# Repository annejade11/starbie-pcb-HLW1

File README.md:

# Cheesie PCB

In this project, I used the pre-existing Starbie tutorial repo by SharKingStudios to make my own "Cheesie" PCB build for week one of the Half Life challenge.

Before this project, I had never worked with PCBs or physical hardware before, but it's something I've been meaning to get into for a long time as I started coding a bit over a year ago. Ever since I started coding and 3D printing things on printers at my school, I just thought it would be so cool to be able to code my own product, then put it together in hardware and print a beautiful design for it. The concept of being my own little "factory" is so cool to me and this first week of Half Life has been the perfect opportunity for me to start learning something I just haven't made the time for before. 

So let's start with the basics.

What is Starbie?

Starbie is a small pcb with a 128x64 pixel OLED screen that displays a sprite of your choice. It has different activities, like napping or playing, and also has some mood bars for energy, joyfulness, and fullness. The tutorial repo describes it as a kind of "desktop tomadachi" and I honestly think that's a perfect description. It uses a DHT11 to detect temperature and humidity as well as an MPU6050 to detect movement, so it senses when you shake it and gives you a digital reaction. It's super cute and the tutorial makes it very beginner friendly.

My Process

Part 1: Hardware

The first part of building Starbie is designing it. I chose to use KiCad, as that's what's recommended by Half Life and also what the tutorial repo uses. I followed the instructions to design the schematic, which is basically all the components you're going to need labeled with what each output/input is recieving/sending.

Here's what mine looked like:

The next step in PCB design is routing, which means visually connecting everything so that you know where all the soldering and stuff is going to go. Because the lines can't cross over each other otherwise signals will mix, this step is super important because you're making sure everything can be connected. In my experience with Starbie, I actually had to change the order of ports (as well as the rotation and positioning of components) multiple times because I would end up in a situation where a connection couldn't get from A to B without crossing over a bunch of other connections. I also learned that the board has two sides, so some connections which just couldn't all fit on the front went on the back side of the PCB. I added some cute stickers to the PCB too (as well as some holes for mounting, but this is fully optional I just figured I might want to screw my PCB into a case). 

Here's the final result:

The red connections are the front, while that one thick blue line is what I have on the back of the PCB.

KiCad also has a really cool feature where you can see a 3D rendering of your PCB once you've routed it.

Seeing a (kind of) physical rendering of my work was super gratifying.

Part 2: Software

The next part of building Starbie was to do the code. The tutorial repo actually gives you a set of code already in case you don't know how, but I wanted to do some of it myself. Unfortunately, I didn't have the time to really dig into it as much as I might have liked, but I still wanted to customize it. (Note: I did have to edit the ports as I ended up moving them around in a different placement than the tutorial did, and anyone doing this should verify they have the same ports as what's in the code!)

The first thing I did was make my own sprite. I used a web-based sprite generator (not AI, just a platform that lets you draw pixelated sprites) called piskel. I made a fun little Peacock who remains unnamed, but I think she turned out very cute! For now I'll just go with Princess because the word "Peacock" contains the word "Pea" which reminds me of the Princess and the Pea, but I promise I'll choose something better later. 

Then, because you can't just drag and drop an image into code and say "draw this", I used a link from the tutorial to turn the photo into code. Here's what that looked like when it was done:

While I can't say I understand how every number works, my impression is that it's instructions that tell the code if each pixel on a 32 x 32 pixel grid is black or white. The screen I'm using can only display one color, which is white, (plus black when it's off), so the code shouldn't need to specify the exact shade of blue or gray for each pixel.

Note: Much of the following section is explaining functions and if statements for non-coders. If you already know this, you can skip to the image in which I create a function "drawBubbles" to display bubbles whenever the pet is in "PLAY" mode.

The other thing I wanted to do to customize my code was a small effect. The tutorial walks you through adding a sparkle effect, and I decided this was something I could easily do myself without needing to understand all the code. The example essentially created a new custom function that drew a sparkle. Then, it set that function to be called repeatedly at specific time intervals while the pet was in "nap" mode. For people who aren't coders, a function is basically a set of instructions. If you don't show it to anyone, nothing gets done and its as if it didn't exist in the first place. This is why you need to "call" the function. Calling a function is when you reference these instructions somewhere else in your code. For example, imagine you told a friend, "whenever you open the door, follow protocol 5". Without knowing what protocol 5 is, your friend is confused and does not know what to do. But if you tell your friend, "whenever you open the door, follow protocol 5" and then give your friend a seperate sheet of paper which reads, "Protocol 5: first, close the door, then take your key, then lock the door", your friend now knows what to do. Protocol 5 has basically become an abbreviation, or a faster way to reference the instructions without needing to say them each time. That's what functions do to the computer. You give it a condition, the computer version of "whenever you open the door", and then give it the instructions to do when that statement is true. So getting back to the focus, I made a new custom function / protocol called drawBubbles. I then set it to activate whenever the pet was in "PLAY" mode so you get a cute little bubble at a random spot on the screen. I designed the bubble myself (again on piskel) and then gave the instructions to the computer on how to draw it. This time, I did it manually, with a function called drawPixel. You give drawPixel the x and y coordinate of your pixel on the Cartesian plane (think of the graphs from your math classes but 0,0 is the top left corner of your screen) as well as the color of the pixel, and it'll draw it. I set this a little more fancily (is that a word?) and used a placeholder for my x and y coordinates creatively named "x" and "y". Whenever the function is called, the sentence which tells the computer to run the instructions will also have to include the x it wants to use and the y it wants to use. Going back to the door example, this is as if you set the "door" in protocol 5 to be a placeholder. Then, you tell your friend, "whenever you open the door, follow protocol 5 specifically for the door you just opened". This allows you to write one protocol and it'll work for when your friend leaves through the front door, the back door, or even the garage door. They won't open the front door and then go around to close and lock the back door, because you told your friend to follow the protocol for the door they just opened. I used this system to write my code for the bubble, so when I type things like "x+2" it means "whatever x coordinate you're using, but add 2". I treat the placeholders "x" and "y" as my (0,0) and build everything else relative to that—one to the right of 0,0, one to the right and one down from 0,0, etc.

Also what the bubble looks like for anyone who was curious (the red dot represents 0,0 or the origin):

Yay! The code is finally done, and so is the hardware design. Starbie accomplished!

But WAIT! There's more!

Bonus Part: Designing the case

I wanted to add more to this PCB, but I'd reached the end of my expertise code and hardware wise. So instead, I went with something I'm a bit better at: CAD, or computer aided design. This is digitally designing or creating a 3D object which can then be manufactured, for example by printing your model with a 3D printer. I decided to use these (still slightly limited) CAD skills of mine for good and make a case for my PCB. Originally, the theme for the PCB was supposed to be planet themed, so I wanted to make a planet keychain. I spent some time on that, and honeslty, it looked okay. Here's a glimpse:

However, this planet had a lot of issues. I designed it by hollowing out the inside for the PCB, but because of the curve on the planet and the fact that the screen is... well... decidedly less curved, I couldn't push the display up so that it was flush with the outside of the planet since the display would be attached to the rest of the PCB which would not fit on any of the faces of the planet. This was not ideal, as it meant I had to open the keychain just to see inside it. I decided I did not like this one bit, so it was time for a redesign. I instead made a cheese keychain (another thing I'm passionate about—look, cheese is really good) and because it was a block of cheese I could use the flat sides to make cutouts for the screen and buttons. Here's the final product, with the blue piece being the front and the gray piece being the back:

View of the inside of the blue piece where space for the PCB and usb cable were cut out:

And yes, this is where the name "Cheesie" originated from. It's kind of corny, I know, but I still think it's cute. The holes in the back piece also allow for better air circulation which is good because the pcb needs to be able to read the humidity and tempeerature of the air around it (remember how I mentioned the MPU 6050 does that?).

So that's the PCB. Design, code, and case, all ready to go.

Softwares:
Here are all the programs I used as well as their respective purposes.
PCB design & routing - KiCad
Sprite/Pixel art making - Piskel (web-based)
Code - Arduino IDE
Case CAD - Onshape (web-based)

All these are free to use for students (onshape may require you to pay if you're not a student but I'm not sure).

From the digital to the physical:

The next step is obviously to build the PCB. I'm not doing that until week 5 of the Half Life project (if my project gets approved fingers crossed) so I'll have to get back to you on the actual building part. Still, there's a digital aspect to the building, and that's called the BOM, or the Bill of Materials. In case you didn't get it from the title, the BOM is just a list of all the parts you're going to need, how much they are, and where you're getting them from. Here's mine:

A couple things to note about my BOM:
1) THIS DOES NOT INCLUDE TOOLS. This is just a list of any parts I'd need, there are additional required tools that aren't on here.
2) I have two items on there listed as $0.01. No, I did not find a really awesome deal on key caps and key switches, I actually have some at home. I bought key switches for my 3D printing and I plan on printing some key caps so I don't have to buy them. However, I've left them on the bill of materials because even though I'm not buying them they are still necessary for my project.

Even though it's been a bit stressful trying to finish this on time, I am super grateful for Half Life for giving me tutorials and making it so easy to start learning something interesting. We take the path of least resistance, after all, and Half Life has really made sure there's very little resistance there. I've had lots of fun learning and I hope I'll get to keep building on it. I'm incredibly excited to build this for real in a couple weeks and also super proud of myself for finishing it considering I started on day 5 out of 7 because of school work and wasn't sure I'd have the determination to do it all. Good luck to anyone attempting the same thing and congratulations to all those who've also built starbies of their own this week!

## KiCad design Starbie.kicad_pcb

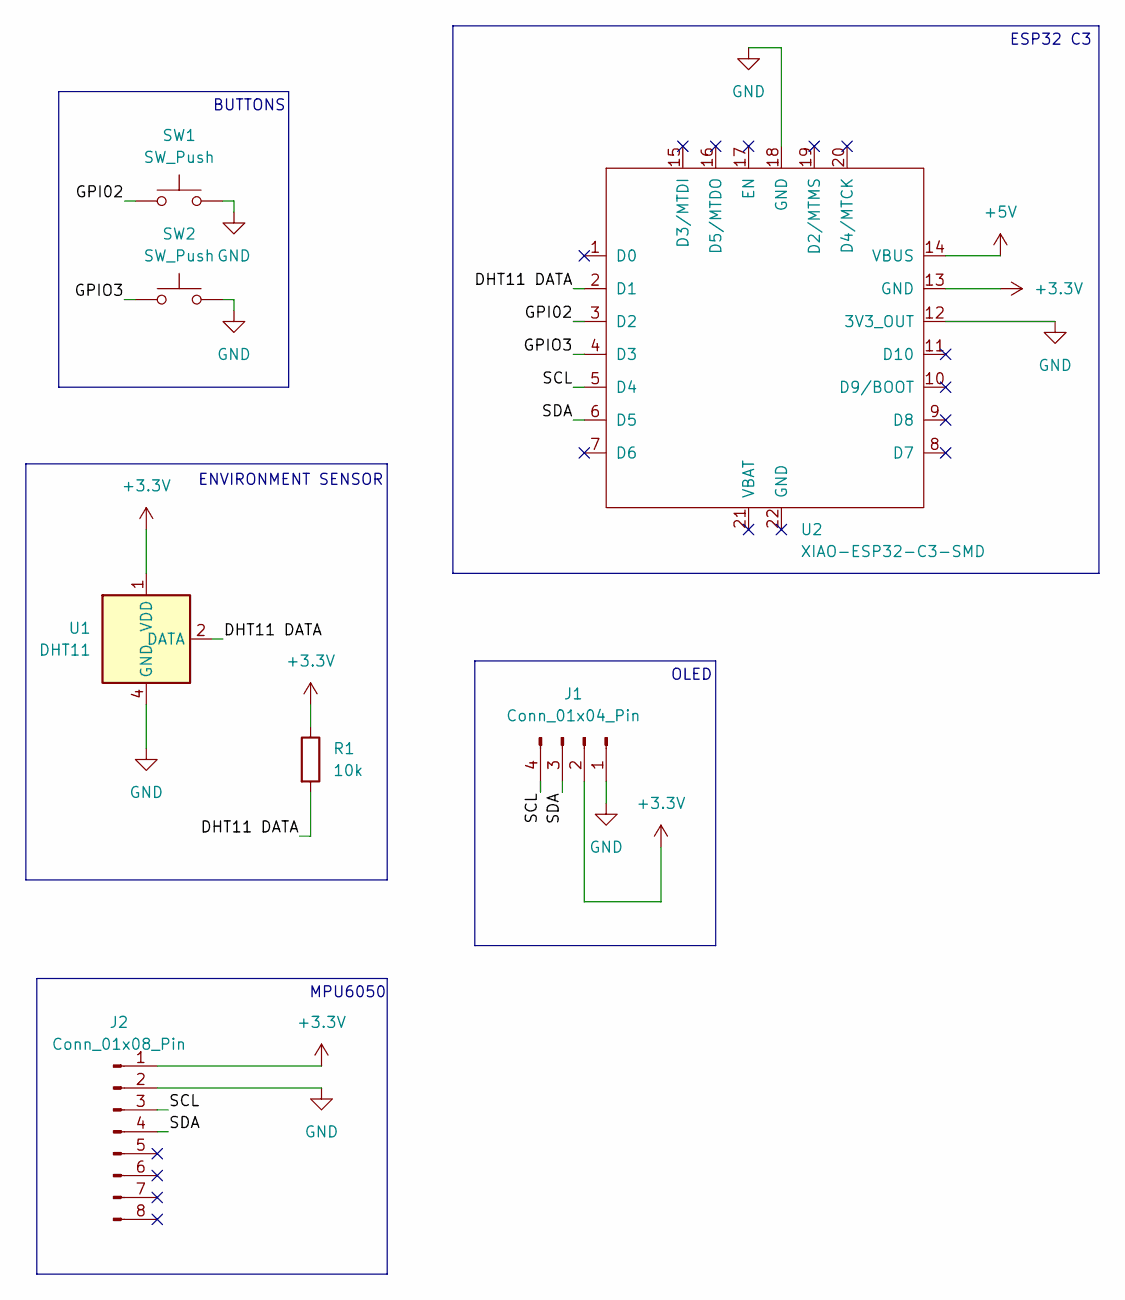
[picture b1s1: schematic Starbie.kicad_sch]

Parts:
J1: Conn_01x04_Pin; Display_128x64_096_I2C
J2: Conn_01x08_Pin; PinHeader_1x08_P2.54mm_Horizontal
R1: 10k; R_Axial_DIN0204_L3.6mm_D1.6mm_P7.62mm_Horizontal
SW1, SW2: SW_Push; SW_Cherry_MX_1.00u_PCB
U1: DHT11; Aosong_DHT11_5.5x12.0_P2.54mm
U2: XIAO-ESP32-C3-SMD

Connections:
+3.3V: J1.2, J2.1, R1.1, U1.1 (VDD), U2.13 (GND)
+5V: U2.14 (VBUS)
/DHT11 DATA: R1.2, U1.2 (DATA), U2.2 (D1)
/GPI02: SW1.1, U2.3 (D2)
/GPIO3: SW2.1, U2.4 (D3)
/SCL: J1.4, J2.3, U2.5 (D4)
/SDA: J1.3, J2.4, U2.6 (D5)
GND: J1.1, J2.2, SW1.2, SW2.2, U1.4 (GND), U2.12 (3V3_OUT), U2.18 (GND)

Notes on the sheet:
ESP32 C3
MPU6050
OLED
ENVIRONMENT SENSOR
BUTTONS

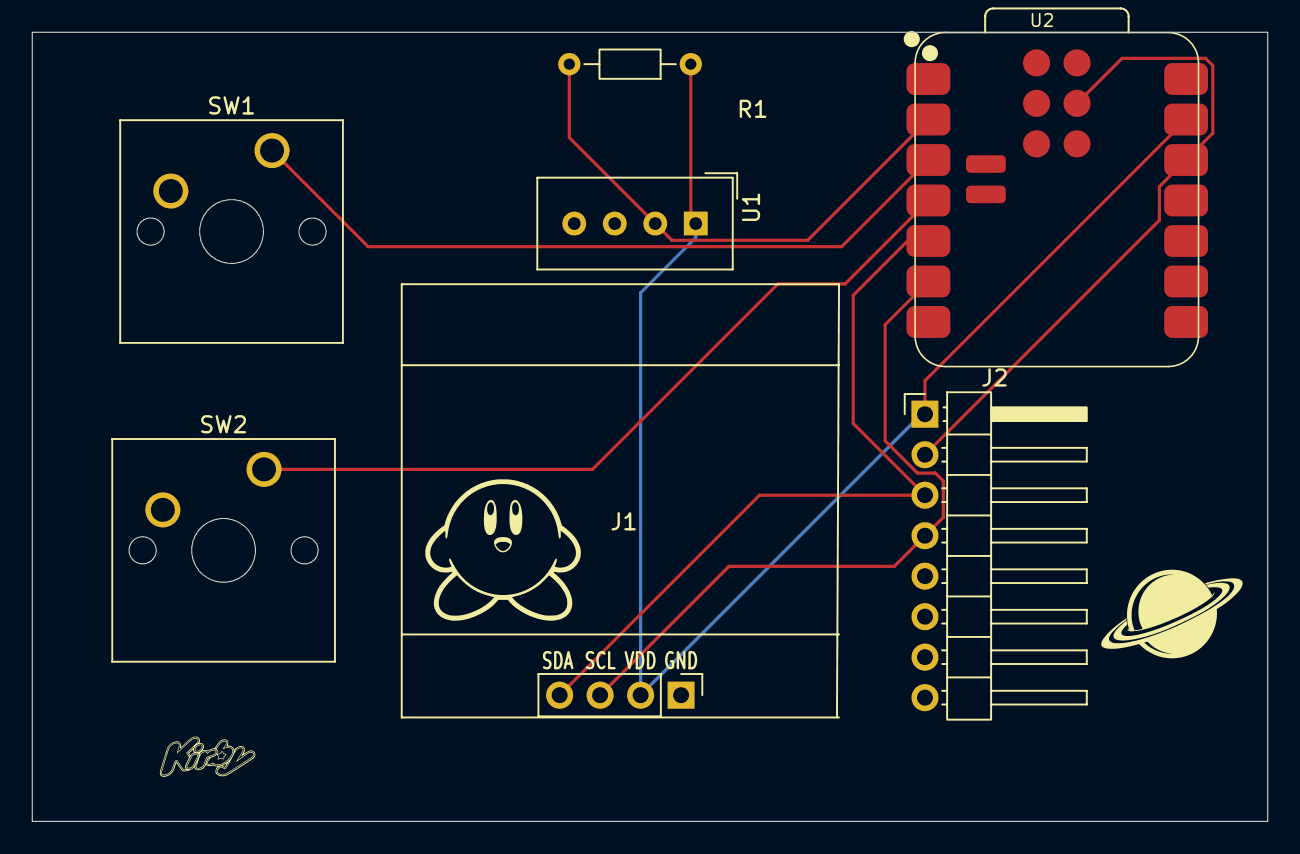
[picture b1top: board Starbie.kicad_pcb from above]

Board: 2 copper layers, 77.5 x 49.5 mm, 7 parts (0 on the bottom side), 7 nets.
